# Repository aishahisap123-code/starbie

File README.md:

# Starcade35
Starcade is a motion-controlled handheld arcade pet and retro game console. Inspired by classic handhelds and desktop pets, it brings interactive games, motion sensing, and sound effects together in a custom wing-shaped PCB. Instead of relying solely on traditional buttons, you interact with games, menus, and pet reactions by physically tilting, shaking, and rotating the board.

# What It Is
Starcade is designed to sit on your desk, display custom animations on a bright OLED screen, and react directly to how you handle it. Tilting, rotating the encoder, pressing action buttons, and listening to sound effects and LED animations are all core to the physical experience.

Virtual Pet Simulator   
- Walking & Animations: Watch your pet walk back and forth across the screen automatically.   
- Nap Mode: Put your pet to sleep to recover its energy levels over time.   
- Stats Tracking: Monitor and update your pet's current Joy, Energy, and Fullness stats, which are saved automatically to the board's non-volatile memory.   

Environment & Sensor Monitoring   
- Temperature & Humidity: Reads ambient room data in real-time using a connected DHT11 sensor.   
- Tilt Controls: Uses an MPU6050 accelerometer to detect board tilts and shakes for navigating menus and playing games.   

Built-In Mini-Games   
- Dodge Game: An obstacle-avoidance game where you tilt the board to move your player up and down and score points.   
- Reflex Test: A reaction-speed challenge that tests how fast you can hit the button when the signal goes live.   
- Snake Game: The classic retro grid-based game where you guide a growing snake to eat food without hitting the walls or its own tail.

Hardware & Audio-Visual Extras   
- NeoPixel Light Show: Dynamic, colorful lighting patterns that cycle across your LED strip.   
- Sound Effects & Test Mode: Generates various audio tones and alerts through the buzzer for games and button presses.

The board includes an ESP32-C3 microcontroller, 0.96" OLED display, 6-axis MPU6050 motion sensor, DHT11 temperature/humidity sensor, addressable WS2812B RGB LEDs, active buzzer, and a rotary encoder inside a compact wing-shaped PCB design. It is USB-C powered and optimized for easy component assembly and custom firmware hacking.

# Why?
This project was created as a complete, hands-on hardware and embedded software tutorial, taking builders all the way from custom PCB layout and Gerber manufacturing to writing full Arduino firmware from scratch.

# Project Status
The custom PCB layout, ground plane generation, Gerber manufacturing exports, and component DRC checks are complete and verified. Starter Arduino IDE code and pin assignment maps are set up to handle display drivers, motion detection, RGB lighting, and menu navigation.

# Software
Firmware/ contains modular, self-contained Arduino IDE sketches for the Seeed Studio XIAO ESP32-C3. Builders customize pin assignments, motion sensitivity, sound effects, LED lighting modes, and sensor readouts at the top of the sketch. See the Firmware/ README for library setup, board manager links, and flashing instructions.

# Repository Contents
PCB/ — KiCad source files, schematic diagrams, and ready-to-upload Gerber fabrication exports (.zip)

Renders/ — 2D/3D front and back PCB renders with custom silkscreen artwork (STARCADE35, AXISAP, and emblems)

Project Guide.md — Step-by-step assembly, soldering, and manufacturing guide

Firmware/ — Arduino IDE starter sketches for OLED graphics, MPU6050 motion tracking, DHT11 environmental readings, WS2812B LEDs, buzzer audio, and rotary menu navigation

BOM/ Starcade 35 – bill of materials
| Week | Tier | Parts funding |
| --- | --- | --- |
| Week 1 | Tier 1 | $30.00 |

| Part | What it's for | Qty | Unit | Total | Vendor |
| --- | --- | --- | --- | --- | --- |
| [ESP32 c3 mini](https://www.aliexpress.com/item/1005008791937363.html?spm=a2g0o.cart.0.0.3c4d38daD6macX&mp=1&pdp_npi=6%40dis%21GBP%21GBP+7.09%21GBP+7.09%21%21GBP+5.97%21%21%21%402103973d17915527209206815e14b1%2112000052930246748%21ct%21UK%213165619755%21%211%210%21) | The main brain that runs your software, handles Wi-Fi/Bluetooth, and controls all components. | 1 | $8.34 | $8.34 | [Aliexpress](https://www.aliexpress.com/item/1005008791937363.html?spm=a2g0o.cart.0.0.3c4d38daD6macX&mp=1&pdp_npi=6%40dis%21GBP%21GBP+7.09%21GBP+7.09%21%21GBP+5.97%21%21%21%402103973d17915527209206815e14b1%2112000052930246748%21ct%21UK%213165619755%21%211%210%21) |
| [MPU-6050 MPU6050 Module](https://www.aliexpress.com/item/1005009668682906.html?spm=a2g0o.cart.0.0.3c4d38daD6macX&mp=1&pdp_npi=6%40dis%21GBP%21GBP+2.09%21GBP+2.09%21%21GBP+1.76%21%21%21%402103973d17915527209206815e14b1%2112000049816725556%21ct%21UK%213165619755%21%211%210%21) | accelerometer and gyro used for tilt-based motion controls in games. | 1 | $1.73 | $1.73 | [Aliexpress](https://www.aliexpress.com/item/1005009668682906.html?spm=a2g0o.cart.0.0.3c4d38daD6macX&mp=1&pdp_npi=6%40dis%21GBP%21GBP+2.09%21GBP+2.09%21%21GBP+1.76%21%21%21%402103973d17915527209206815e14b1%2112000049816725556%21ct%21UK%213165619755%21%211%210%21) |
| [DHT11](https://www.aliexpress.com/item/1005008953430940.html?spm=a2g0o.cart.0.0.511138da3StELt&mp=1&pdp_npi=6%40dis%21GBP%21GBP+1.06%21GBP+1.06%21%21GBP+0.88%21%21%21%400b884a9917915535706416768e0d2b%2112000047346503744%21ct%21UK%213165619755%21%211%210%21) | temp sensor | 1 | $1.40 | $1.40 | [Aliexpress](https://www.aliexpress.com/item/1005008953430940.html?spm=a2g0o.cart.0.0.511138da3StELt&mp=1&pdp_npi=6%40dis%21GBP%21GBP+1.06%21GBP+1.06%21%21GBP+0.88%21%21%21%400b884a9917915535706416768e0d2b%2112000047346503744%21ct%21UK%213165619755%21%211%210%21) |
| [pcb board](https://cart.jlcpcb.com/shopcart/cart) | pcb | 1 | $8.67 | $8.67 | [JLCPCB](https://cart.jlcpcb.com/shopcart/cart) |
| [0.96  inch OLED](https://www.aliexpress.com/item/1005006141235306.html?spm=a2g0o.cart.0.0.578f38dab9qQyl&mp=1&pdp_npi=6%40dis%21GBP%21GBP+2.26%21GBP+0.70%21%21GBP+0.33%21%21%21%4021613be817915538824665149e0ef0%2112000035944225408%21ct%21UK%213165619755%21%211%210%21) | the display | 1 | $0.93 | $0.93 | [Aliexpress](https://www.aliexpress.com/item/1005006141235306.html?spm=a2g0o.cart.0.0.578f38dab9qQyl&mp=1&pdp_npi=6%40dis%21GBP%21GBP+2.26%21GBP+0.70%21%21GBP+0.33%21%21%21%4021613be817915538824665149e0ef0%2112000035944225408%21ct%21UK%213165619755%21%211%210%21) |
| [rotary encoder](https://www.aliexpress.com/item/1005008583446552.html?spm=a2g0o.productlist.main.2.322d6a57Omemmf&algo_pvid=290e5376-c6e0-4d74-8f15-2345f59ad43f&algo_exp_id=290e5376-c6e0-4d74-8f15-2345f59ad43f-1&pdp_ext_f=%7B%22order%22%3A%221189%22%2C%22spu_best_type%22%3A%22price%22%2C%22eval%22%3A%221%22%2C%22fromPage%22%3A%22search%22%7D&pdp_npi=6%40dis%21GBP%213.93%213.15%21%21%215.05%214.05%21%40210393bd17915540235537215e0cdb%2112000045835073058%21sea%21UK%213165619755%21X%211%210%21n_tag%3A-29919%3Bd%3Ae4ba77da%3Bm03_new_user%3A-29895%3BpisId%3A5000000218189468&curPageLogUid=ELZrBR1cT0gn&utparam-url=scene%3Asearch%7Cquery_from%3A%7Cx_object_id%3A1005008583446552%7C_p_origin_prod%3A) | navigation | 1 | $5.20 | $5.20 | [Aliexpress](https://www.aliexpress.com/item/1005008583446552.html?spm=a2g0o.productlist.main.2.322d6a57Omemmf&algo_pvid=290e5376-c6e0-4d74-8f15-2345f59ad43f&algo_exp_id=290e5376-c6e0-4d74-8f15-2345f59ad43f-1&pdp_ext_f=%7B%22order%22%3A%221189%22%2C%22spu_best_type%22%3A%22price%22%2C%22eval%22%3A%221%22%2C%22fromPage%22%3A%22search%22%7D&pdp_npi=6%40dis%21GBP%213.93%213.15%21%21%215.05%214.05%21%40210393bd17915540235537215e0cdb%2112000045835073058%21sea%21UK%213165619755%21X%211%210%21n_tag%3A-29919%3Bd%3Ae4ba77da%3Bm03_new_user%3A-29895%3BpisId%3A5000000218189468&curPageLogUid=ELZrBR1cT0gn&utparam-url=scene%3Asearch%7Cquery_from%3A%7Cx_object_id%3A1005008583446552%7C_p_origin_prod%3A) |
| [buzzer](https://www.aliexpress.com/item/1005008789575850.html?spm=a2g0o.cart.0.0.175238daobE0Ld&mp=1&pdp_npi=6%40dis%21GBP%21GBP+1.38%21GBP+1.38%21%21GBP+1.34%21%21%21%400b0fed2b17915543499984784e1024%2112000046671331943%21ct%21UK%213165619755%21%211%210%21) | make sound | 1 | $1.82 | $1.82 | [Aliexpress](https://www.aliexpress.com/item/1005008789575850.html?spm=a2g0o.cart.0.0.175238daobE0Ld&mp=1&pdp_npi=6%40dis%21GBP%21GBP+1.38%21GBP+1.38%21%21GBP+1.34%21%21%21%400b0fed2b17915543499984784e1024%2112000046671331943%21ct%21UK%213165619755%21%211%210%21) |
| [buttons](https://www.aliexpress.com/item/1005001629177989.html?spm=a2g0o.productlist.main.2.2b7a4c01fzW9qP&algo_pvid=2075475e-6f89-4258-8f3a-6f83f7748477&algo_exp_id=2075475e-6f89-4258-8f3a-6f83f7748477-1&pdp_ext_f=%7B%22order%22%3A%223471%22%2C%22eval%22%3A%221%22%2C%22fromPage%22%3A%22search%22%7D&pdp_npi=6%40dis%21GBP%211.13%210.35%21%21%219.71%212.99%21%400b1585c117915547239767987e0cff%2112000028585601895%21sea%21UK%213165619755%21X%211%210%21n_tag%3A-29919%3Bd%3Ae4ba77da%3Bm03_new_user%3A-29895%3BpisId%3A5000000218189468&curPageLogUid=qgexuiVhkgyf&utparam-url=scene%3Asearch%7Cquery_from%3A%7Cx_object_id%3A1005001629177989%7C_p_origin_prod%3A) | navigation and menu and gameplay | 1 | $1.61 | $1.61 | [Aliexpress](https://www.aliexpress.com/item/1005001629177989.html?spm=a2g0o.productlist.main.2.2b7a4c01fzW9qP&algo_pvid=2075475e-6f89-4258-8f3a-6f83f7748477&algo_exp_id=2075475e-6f89-4258-8f3a-6f83f7748477-1&pdp_ext_f=%7B%22order%22%3A%223471%22%2C%22eval%22%3A%221%22%2C%22fromPage%22%3A%22search%22%7D&pdp_npi=6%40dis%21GBP%211.13%210.35%21%21%219.71%212.99%21%400b1585c117915547239767987e0cff%2112000028585601895%21sea%21UK%213165619755%21X%211%210%21n_tag%3A-29919%3Bd%3Ae4ba77da%3Bm03_new_user%3A-29895%3BpisId%3A5000000218189468&curPageLogUid=qgexuiVhkgyf&utparam-url=scene%3Asearch%7Cquery_from%3A%7Cx_object_id%3A1005001629177989%7C_p_origin_prod%3A) |
| **Parts subtotal** | — | — | — | **$29.70** | — |
| **Tax & shipping** | — | — | — | **$0.00** | — |
| **Total** | — | — | — | **$29.70** | — |

$0.30 left of the tier's funding.

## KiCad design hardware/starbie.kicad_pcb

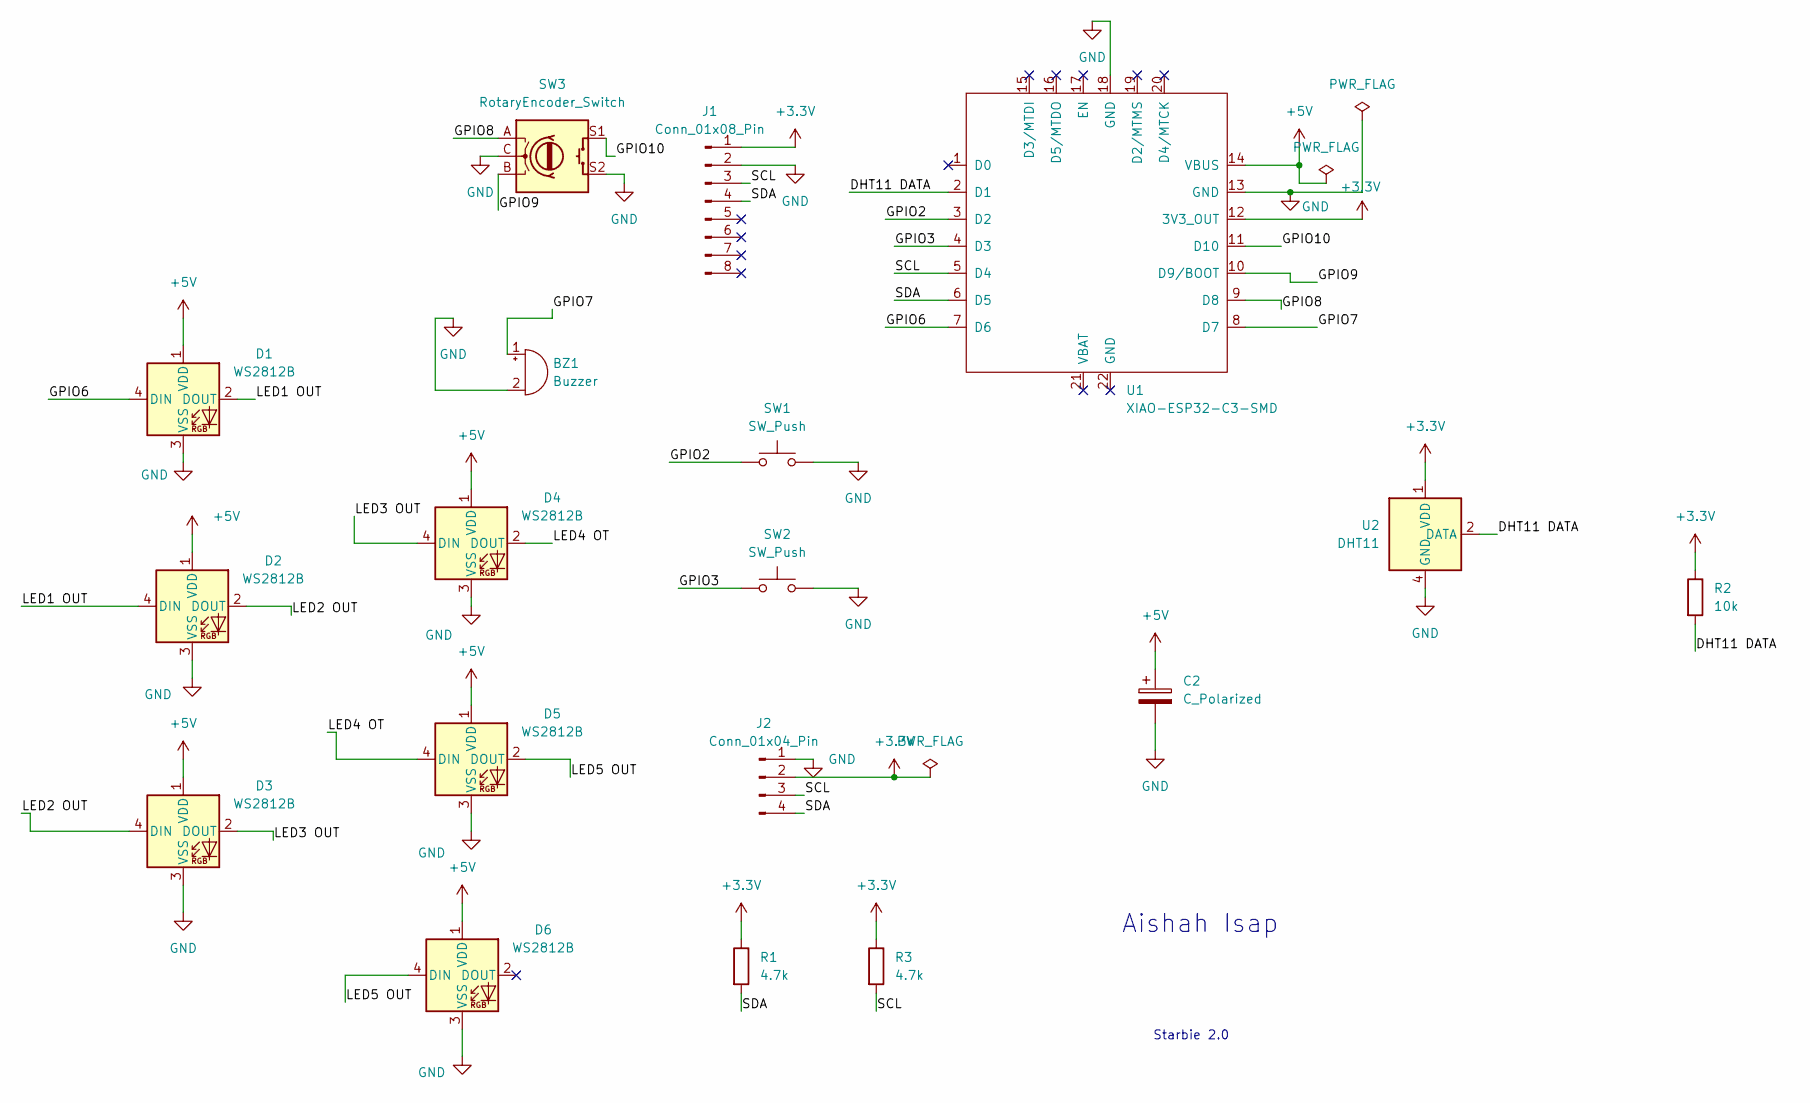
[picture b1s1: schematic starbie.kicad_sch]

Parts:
BZ1: Buzzer; Buzzer_12x9.5RM7.6
C2: C_Polarized; CP_Radial_D8.0mm_P3.50mm
D1, D2, D3, D4, D5, D6: WS2812B; LED_WS2812B_PLCC4_5.0x5.0mm_P3.2mm
J1: Conn_01x08_Pin; MPU6050_Module
J2: Conn_01x04_Pin; Display_128x64_096_I2C
R1, R3: 4.7k; R_Axial_DIN0204_L3.6mm_D1.6mm_P7.62mm_Horizontal
R2: 10k; R_Axial_DIN0204_L3.6mm_D1.6mm_P7.62mm_Horizontal
SW1, SW2: SW_Push; SW_PUSH_6mm
SW3: RotaryEncoder_Switch; RotaryEncoder_Alps_EC11E-Switch_Vertical_H20mm
U1: XIAO-ESP32-C3-SMD; MCU_Seeed_ESP32C3
U2: DHT11; Aosong_DHT11_5.5x12.0_P2.54mm

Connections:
+3.3V: J1.1, J2.2, R1.1, R2.1, R3.1, U1.12 (3V3_OUT), U2.1 (VDD)
+5V: C2.1, D1.1 (VDD), D2.1 (VDD), D3.1 (VDD), D4.1 (VDD), D5.1 (VDD), D6.1 (VDD), U1.14 (VBUS)
/DHT11 DATA: R2.2, U1.2 (D1), U2.2 (DATA)
/GPIO2: SW1.1, U1.3 (D2)
/GPIO3: SW2.1, U1.4 (D3)
/GPIO6: D1.4 (DIN), U1.7 (D6)
/GPIO7: BZ1.1 (+), U1.8 (D7)
/GPIO8: SW3.A, U1.9 (D8)
/GPIO9: SW3.B, U1.10 (D9/BOOT)
/GPIO10: SW3.S1, U1.11 (D10)
/LED1 OUT: D1.2 (DOUT), D2.4 (DIN)
/LED2 OUT: D2.2 (DOUT), D3.4 (DIN)
/LED3 OUT: D3.2 (DOUT), D4.4 (DIN)
/LED4 OT: D4.2 (DOUT), D5.4 (DIN)
/LED5 OUT: D5.2 (DOUT), D6.4 (DIN)
/SCL: J1.3, J2.3, R3.2, U1.5 (D4)
/SDA: J1.4, J2.4, R1.2, U1.6 (D5)
GND: BZ1.2 (-), C2.2, D1.3 (VSS), D2.3 (VSS), D3.3 (VSS), D4.3 (VSS), D5.3 (VSS), D6.3 (VSS), J1.2, J2.1, SW1.2, SW2.2, SW3.C, SW3.S2, U1.13 (GND), U1.18 (GND), U2.4 (GND)

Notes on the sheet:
Starbie 2.0
Aishah Isap

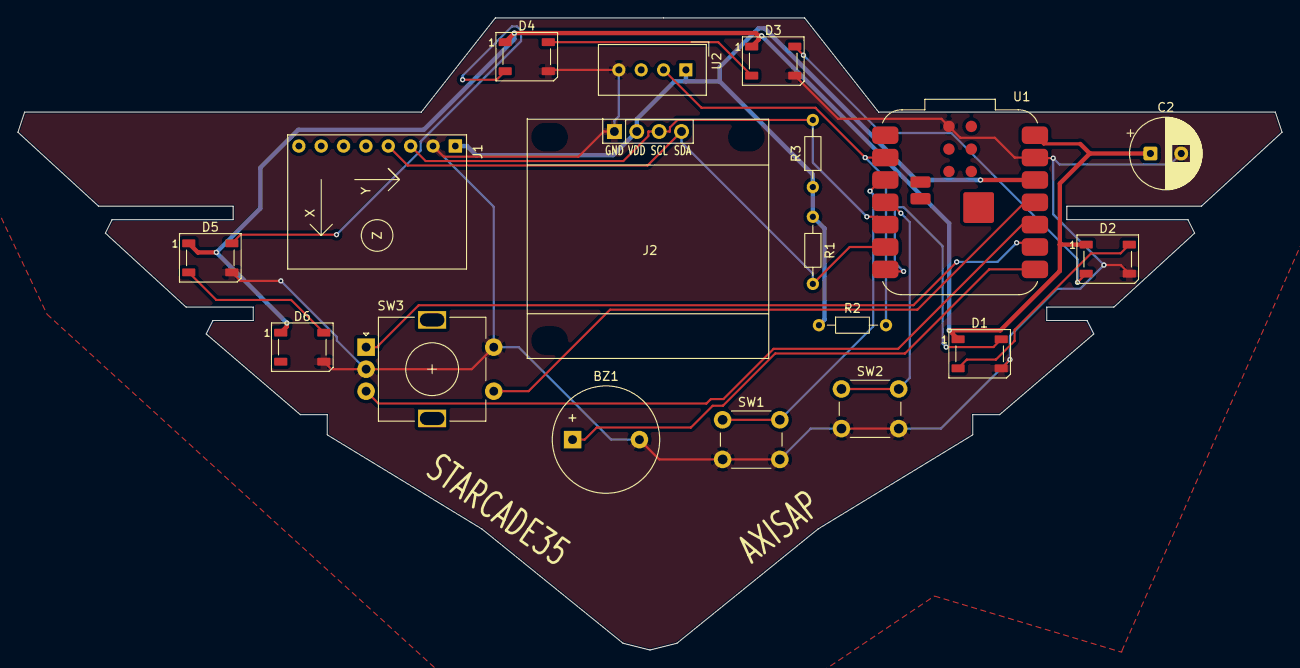
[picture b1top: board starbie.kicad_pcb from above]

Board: 2 copper layers, 143.6 x 71.8 mm, 18 parts (0 on the bottom side), 18 nets.
